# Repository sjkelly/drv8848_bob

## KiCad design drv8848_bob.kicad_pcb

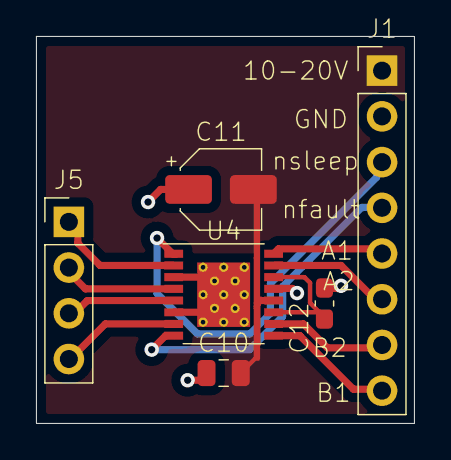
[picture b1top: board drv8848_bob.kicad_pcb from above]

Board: 2 copper layers, 21.0 x 21.5 mm, 6 parts (0 on the bottom side), 13 nets.

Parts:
C10: 0.1uF; C_0805_2012Metric
C11: 10uF; CP_Elec_4x5.4
C12: 2.2uF; C_0603_1608Metric_Pad1.08x0.95mm_HandSolder
J1: Conn_01x08; PinHeader_1x08_P2.54mm_Vertical
J5: Conn_01x04_Female; PinHeader_1x04_P2.54mm_Vertical
U4: DRV8848; TSSOP-16-1EP_4.4x5mm_P0.65mm

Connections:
+12V: C10.2, C11.2, J1.1, U4.12
/sheet604C2040/A1: J5.1, U4.2
/sheet604C2040/A2: J5.2, U4.4
/sheet604C2040/B1: J5.4, U4.7
/sheet604C2040/B2: J5.3, U4.5
A1IN[0]: J1.5, U4.16
A2IN[0]: J1.6, U4.15
B1IN[0]: J1.8, U4.9
B2IN[0]: J1.7, U4.10
GND: C10.1, C11.1, C12.1, J1.2, U4.3, U4.6, U4.13, U4.17
unnamed: C12.2, U4.11, U4.14
nfault[0]: J1.4, U4.8
nsleep[0]: J1.3, U4.1

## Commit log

2021-03-13 init
2021-03-14 finalish
